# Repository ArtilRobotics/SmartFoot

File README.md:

# SmartInsole
hardware y Firmware del proyecto

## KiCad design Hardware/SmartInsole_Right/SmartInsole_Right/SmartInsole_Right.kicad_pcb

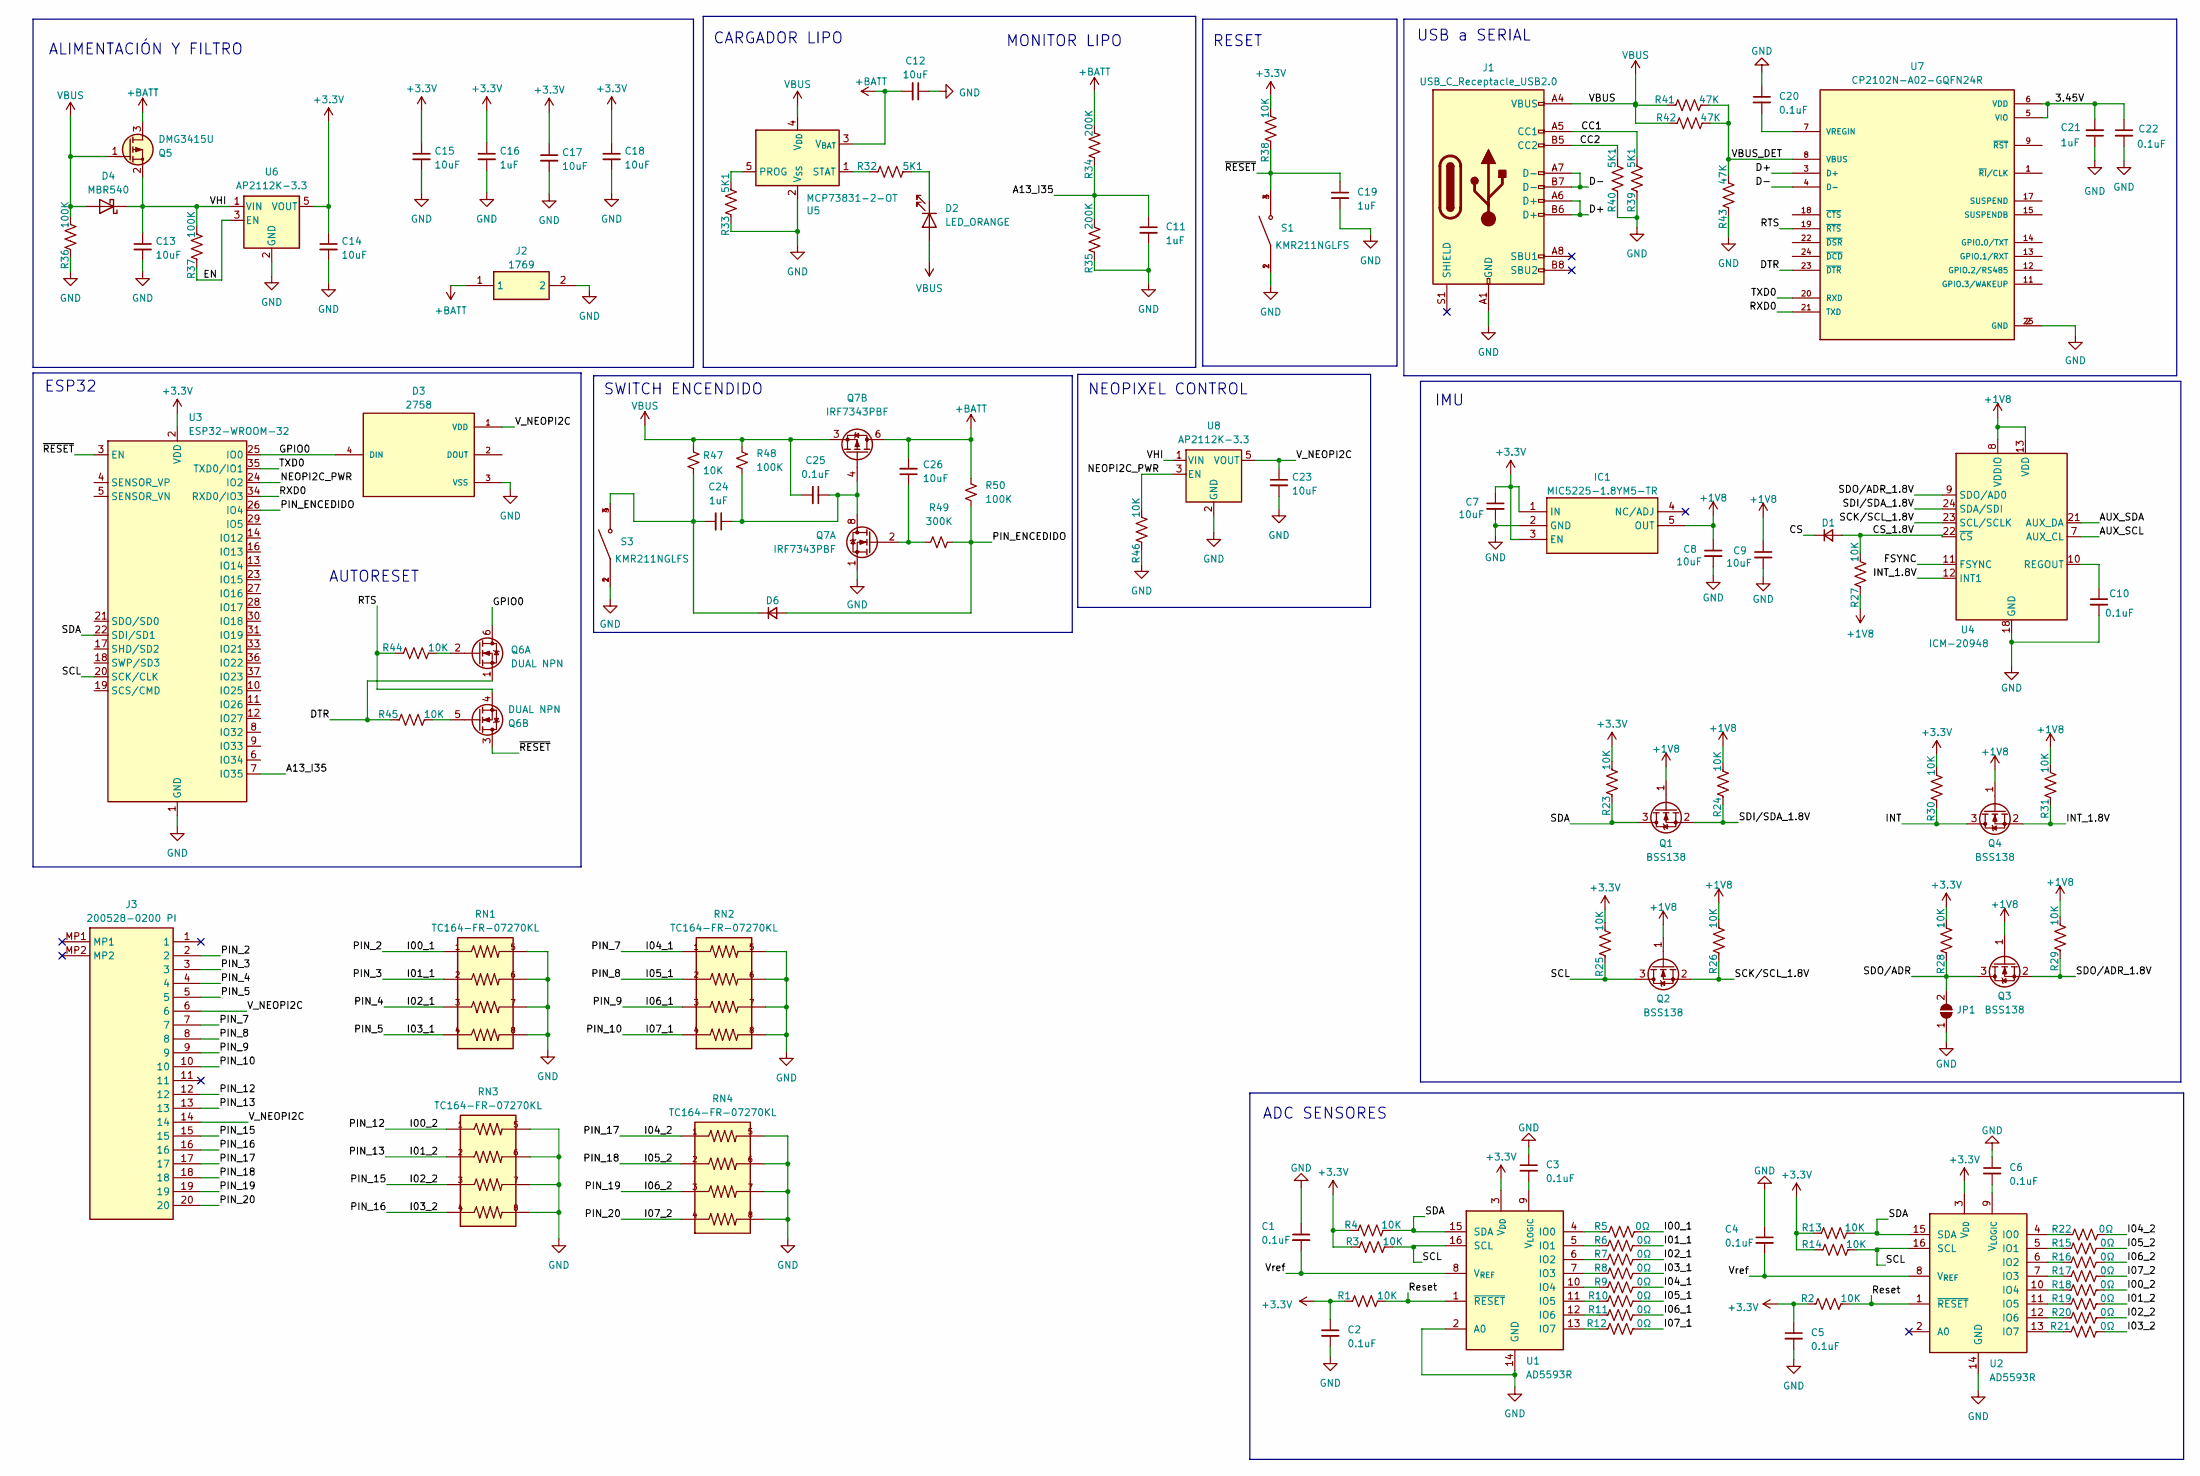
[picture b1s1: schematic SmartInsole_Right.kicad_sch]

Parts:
C1, C2, C3, C4, C5, C6, C10, C20, C22, C25: 0.1uF; C_0805
C7, C8, C9, C12, C13, C14, C15, C17, C18, C23, C26: 10uF; C_0805
C11, C16, C19, C21, C24: 1uF; C_0805
D1, D6: D_Small; D_0805_2012Metric
D2: LED_ORANGE; LED_0805_2012Metric
D3: 2758; SOL320P540X170-4N; PARTREV 01
D4: MBR540; D_SOD-123
IC1: MIC5225-1.8YM5-TR; SOT95P280X130-5N; Mouser Part Number 998-MIC5225-1.8YM5TR
J1: USB_C_Receptacle_USB2.0; USB_C_Receptacle_G-Switch_GT-USB-7010ASV
J2: 1769; Mouser Part Number 485-1769
J3: 200528-0200 PI; 2005280200; Mouser Part Number 538-200528-0200
JP1: SolderJumper_2_Open; SolderJumper-2_P1.3mm_Open_RoundedPad1.0x1.5mm
Q1, Q2, Q3, Q4: BSS138; SOT-23
Q5: DMG3415U; SOT-23
Q6: DUAL NPN
Q7: IRF7343PBF; SOIC-8_3.9x4.9mm_P1.27mm
R1, R2, R3, R4, R13, R14, R23, R24, R25, R26, R27, R28, R29, R30, R31, R38, R44, R45, R46, R47: 10K; R_0805_2012Metric
R5, R6, R7, R8, R9, R10, R11, R12, R15, R16, R17, R18, R19, R20, R21, R22: 0Ω; R_0805_2012Metric
R32, R33, R39, R40: 5K1; R_0805_2012Metric
R34, R35: 200K; R_0805_2012Metric
R36, R37, R48, R50: 100K; R_0805_2012Metric
R41, R42, R43: 47K; R_0805_2012Metric
R49: 300K; R_0805_2012Metric
RN1, RN2, RN3, RN4: TC164-FR-07270KL; RESCAV80P320X160X70-8N
S1, S3: KMR211NGLFS; SW_KMR211NGLFS; PARTREV 8 jun 16
U1, U2: AD5593R; TSSOP-16_4.4x5mm_P0.65mm
U3: ESP32-WROOM-32
U4: ICM-20948; InvenSense_QFN-24_3x3mm_P0.4mm
U5: MCP73831-2-OT; SOT-23-5
U6, U8: AP2112K-3.3; SOT-23-5
U7: CP2102N-A02-GQFN24R; QFN50P400X400X80-25N; PARTREV 1.3

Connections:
+1V8: C8.1, C9.1, IC1.5 (OUT), Q1.1 (G), Q2.1 (G), Q3.1 (G), Q4.1 (G), R24.2, R26.2, R27.1, R29.2, R31.2, U4.8 (VDDIO), U4.13 (VDD)
+3V3: C2.1, C5.1, C7.1, C14.1, C15.1, C16.1, C17.1, C18.1, IC1.1 (IN), IC1.3 (EN), R1.1, R2.1, R3.1, R4.1, R13.1, R14.1, R23.2, R25.2, R28.2, R30.2, R38.2, U1.3 (V_{DD}), U2.3 (V_{DD}), U3.2 (VDD), U6.5 (VOUT)
+BATT: C12.2, C26.2, J2.1, Q5.3 (D), Q7.5 (D), Q7.6 (D), R34.2, R50.1, U5.3 (V_{BAT})
/3.45V: C21.2, C22.1, U7.5 (VIO), U7.6 (VDD)
/A13_I35: C11.1, R34.1, R35.2, U3.7 (IO35)
/AUX_SCL: U4.7 (AUX_CL)
/AUX_SDA: U4.21 (AUX_DA)
/CC1: J1.A5 (CC1), R39.2
/CC2: J1.B5 (CC2), R40.2
/CS: D1.1 (K)
/CS_1.8V: D1.2 (A), R27.2, U4.22 (~CS)
/D+: J1.A6 (D+), J1.B6 (D+), U7.3 (D+)
/D-: J1.A7 (D-), J1.B7 (D-), U7.4 (D-)
/DTR: Q6.1 (S), R45.1, U7.23 (~DTR)
/EN: R37.1, U6.3 (EN)
/FSYNC: U4.11 (FSYNC)
/GPIO0: D3.4 (DIN), Q6.6 (D), U3.25 (IO0)
/I00_1: J3.2, R5.2, RN1.1
/I00_2: J3.12, R18.2, RN3.1
/I01_1: J3.3, R6.2, RN1.2
/I01_2: J3.13, R19.2, RN3.2
/I02_1: J3.4, R7.2, RN1.3
/I02_2: J3.15, R20.2, RN3.3
/I03_1: J3.5, R8.2, RN1.4
/I03_2: J3.16, R21.2, RN3.4
/I04_1: J3.7, R9.2, RN2.1
/I04_2: J3.17, R22.2, RN4.1
/I05_1: J3.8, R10.2, RN2.2
/I05_2: J3.18, R15.2, RN4.2
/I06_1: J3.9, R11.2, RN2.3
/I06_2: J3.19, R16.2, RN4.3
/I07_1: J3.10, R12.2, RN2.4
/I07_2: J3.20, R17.2, RN4.4
/INT: Q4.3 (D), R30.1
/INT_1.8V: Q4.2 (S), R31.1, U4.12 (INT1)
/NEOPI2C_PWR: R46.2, U3.24 (IO2), U8.3 (EN)
/PIN_ENCEDIDO: D6.2 (A), R49.1, R50.2, U3.26 (IO4)
/RTS: Q6.4 (S), R44.1, U7.19 (~RTS)
/RXD0: U3.34 (RXD0/IO3), U7.21 (TXD)
/Reset: R1.2, R2.2, U1.1 (~RESET), U2.1 (~RESET)
/SCK/SCL_1.8V: Q2.2 (S), R26.1, U4.23 (SCL/SCLK)
/SCL: Q2.3 (D), R3.2, R14.2, R25.1, U1.16 (SCL), U2.16 (SCL), U3.20 (SCK/CLK)
/SDA: Q1.3 (D), R4.2, R13.2, R23.1, U1.15 (SDA), U2.15 (SDA), U3.22 (SDI/SD1)
/SDI/SDA_1.8V: Q1.2 (S), R24.1, U4.24 (SDA/SDI)
/SDO/ADR: JP1.2 (B), Q3.3 (D), R28.1
/SDO/ADR_1.8V: Q3.2 (S), R29.1, U4.9 (SDO/AD0)
/TXD0: U3.35 (TXD0/IO1), U7.20 (RXD)
/VBUS_DET: R41.2, R42.2, R43.2, U7.8 (VBUS)
/VHI: C13.1, D4.1 (K), Q5.2 (S), R37.2, U6.1 (VIN), U8.1 (VIN)
/V_NEOPI2C: C23.1, D3.1 (VDD), J3.6, J3.14, U8.5 (VOUT)
/Vref: C1.2, C4.2, U1.8 (V_{REF}), U2.8 (V_{REF})
/~RESET: C19.1, Q6.3 (D), R38.1, S1.3, S1.4, U3.3 (EN)
GND: C1.1, C2.2, C3.1, C4.1, C5.2, C6.1, C7.2, C8.2, C9.2, C10.2, C11.2, C12.1, C13.2, C14.2, C15.2, C16.2, C17.2, C18.2, C19.2, C20.1, C21.1, C22.2, C23.2, D3.3 (VSS), IC1.2 (GND), J1.A1 (GND), J1.A12 (GND), J1.B1 (GND), J1.B12 (GND), J2.2, JP1.1 (A), Q7.1 (S), R33.1, R35.1, R36.1, R39.1, R40.1, R43.1, R46.1, RN1.5, RN1.6, RN1.7, RN1.8, RN2.5, RN2.6, RN2.7, RN2.8, RN3.5, RN3.6, RN3.7, RN3.8, RN4.5, RN4.6, RN4.7, RN4.8, S1.1, S1.2, S3.1, S3.2, U1.2 (A0), U1.14 (GND), U2.14 (GND), U3.1 (GND), U3.15 (GND), U3.38 (GND), U3.39 (GND), U4.18 (GND), U4.20 (GND), U5.2 (V_{SS}), U6.2 (GND), U7.2 (GND), U7.25 (GND), U8.2 (GND)
unnamed: D2.1 (K), R32.2
unnamed: C24.2, D6.1 (K), R47.2, S3.3, S3.4
unnamed: Q6.2 (G), R44.2
unnamed: Q6.5 (G), R45.2
unnamed: C26.1, Q7.2 (G), R49.2
unnamed: C24.1, C25.1, Q7.4 (G), Q7.7 (D), Q7.8 (D), R48.2
unnamed: R5.1, U1.4 (IO0)
unnamed: R6.1, U1.5 (IO1)
unnamed: R7.1, U1.6 (IO2)
unnamed: R8.1, U1.7 (IO3)
unnamed: R9.1, U1.10 (IO4)
unnamed: R10.1, U1.11 (IO5)
unnamed: R11.1, U1.12 (IO6)
unnamed: R12.1, U1.13 (IO7)
unnamed: C3.2, U1.9 (V_{LOGIC})
unnamed: R22.1, U2.4 (IO0)
unnamed: R15.1, U2.5 (IO1)
unnamed: R16.1, U2.6 (IO2)
unnamed: R17.1, U2.7 (IO3)
unnamed: R18.1, U2.10 (IO4)
unnamed: R19.1, U2.11 (IO5)
unnamed: R20.1, U2.12 (IO6)
unnamed: R21.1, U2.13 (IO7)
unnamed: C6.2, U2.9 (V_{LOGIC})
unnamed: C10.1, U4.10 (REGOUT)
unnamed: R33.2, U5.5 (PROG)
unnamed: R32.1, U5.1 (STAT)
unnamed: C20.2, U7.7 (VREGIN)
VBUS: C25.2, D2.2 (A), D4.2 (A), J1.A4 (VBUS), J1.A9 (VBUS), J1.B4 (VBUS), J1.B9 (VBUS), Q5.1 (G), Q7.3 (1), R36.2, R41.1, R42.1, R47.1, R48.1, U5.4 (V_{DD})

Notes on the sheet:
ALIMENTACIÓN Y FILTRO
NEOPIXEL CONTROL
MONITOR LIPO
ADC SENSORES
SWITCH ENCENDIDO
USB a SERIAL
RESET
AUTORESET
CARGADOR LIPO
ESP32
IMU

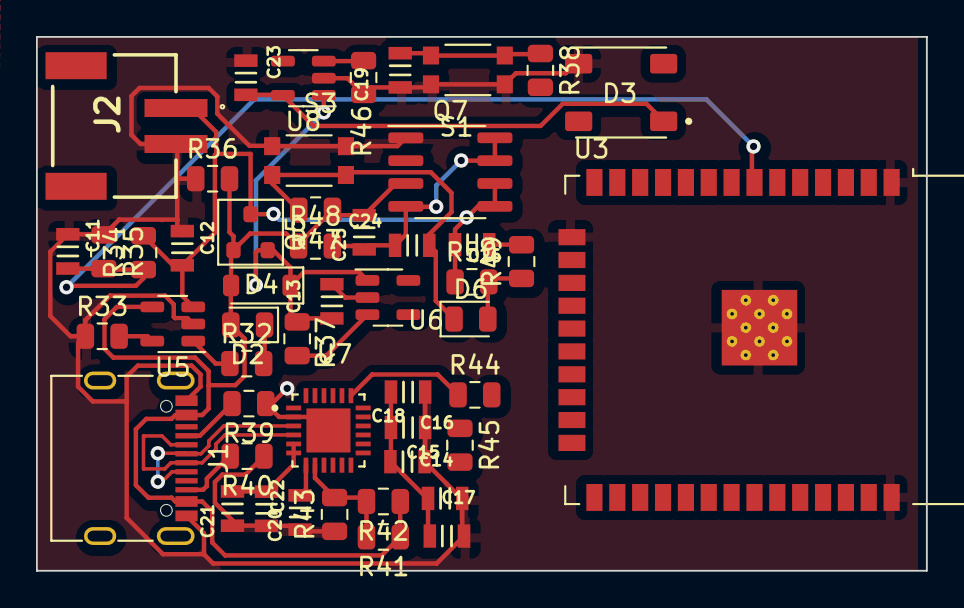
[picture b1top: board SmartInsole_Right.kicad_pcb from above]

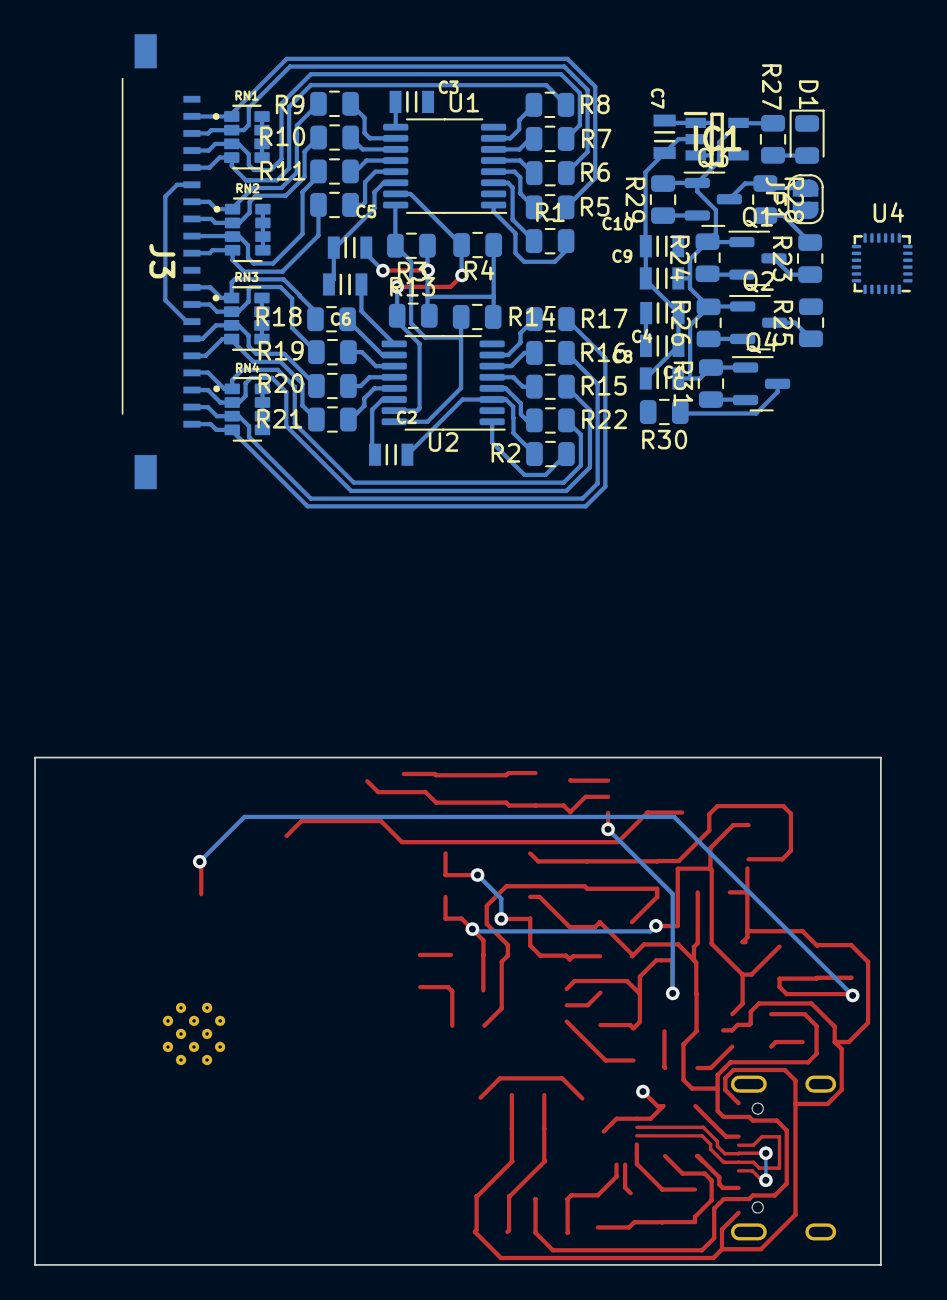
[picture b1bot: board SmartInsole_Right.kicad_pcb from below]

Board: 2 copper layers, 49.4 x 29.7 mm, 106 parts (56 on the bottom side), 76 nets.

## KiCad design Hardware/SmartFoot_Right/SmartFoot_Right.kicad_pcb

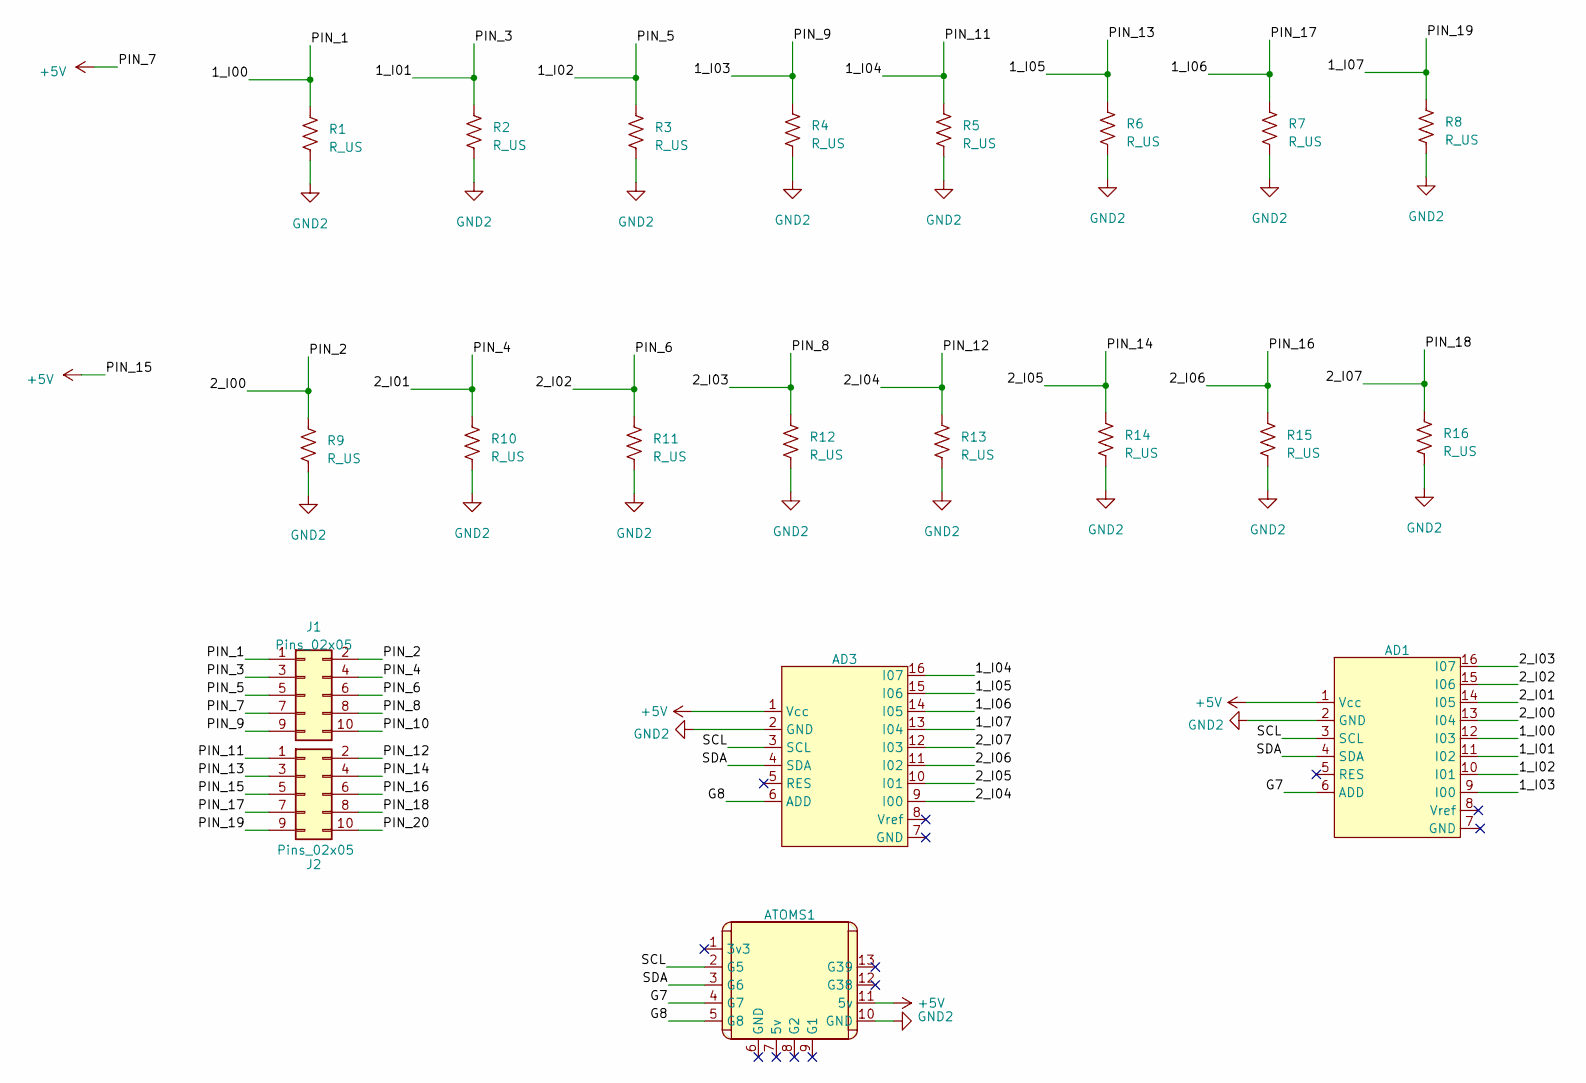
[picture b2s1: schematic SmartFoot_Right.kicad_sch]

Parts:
AD1, AD3: EC Buying AD5593
ATOMS1: ATOM_S3
J1, J2: Pins_02x05; Pins_2x05_2.54mm_TH; Part Number FTSH-105-01-F-DV
R1, R2, R3, R4, R5, R6, R7, R8, R9, R10, R11, R12, R13, R14, R15, R16: R_US; R_0805_2012Metric

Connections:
+5V: AD1.1 (Vcc), AD3.1 (Vcc), ATOMS1.11 (5v), J1.7, J2.5
/1_I00: AD1.12 (I03), J1.1, R1.1
/1_I01: AD1.11 (I02), J1.3, R2.1
/1_I02: AD1.10 (I01), J1.5, R3.1
/1_I03: AD1.9 (I00), J1.9, R4.1
/1_I04: AD3.16 (I07), J2.1, R5.1
/1_I05: AD3.15 (I06), J2.3, R6.1
/1_I06: AD3.14 (I05), J2.7, R7.1
/1_I07: AD3.13 (I04), J2.9, R8.1
/2_I00: AD1.13 (I04), J1.2, R9.1
/2_I01: AD1.14 (I05), J1.4, R10.1
/2_I02: AD1.15 (I06), J1.6, R11.1
/2_I03: AD1.16 (I07), J1.8, R12.1
/2_I04: AD3.9 (I00), J2.2, R13.1
/2_I05: AD3.10 (I01), J2.4, R14.1
/2_I06: AD3.11 (I02), J2.6, R15.1
/2_I07: AD3.12 (I03), J2.8, R16.1
/G7: AD1.6 (ADD), ATOMS1.4 (G7)
/G8: AD3.6 (ADD), ATOMS1.5 (G8)
/PIN_10: J1.10
/PIN_20: J2.10
/SCL: AD1.3 (SCL), AD3.3 (SCL), ATOMS1.2 (G5)
/SDA: AD1.4 (SDA), AD3.4 (SDA), ATOMS1.3 (G6)
GND2: AD1.2 (GND), AD3.2 (GND), ATOMS1.10 (GND), R1.2, R2.2, R3.2, R4.2, R5.2, R6.2, R7.2, R8.2, R9.2, R10.2, R11.2, R12.2, R13.2, R14.2, R15.2, R16.2

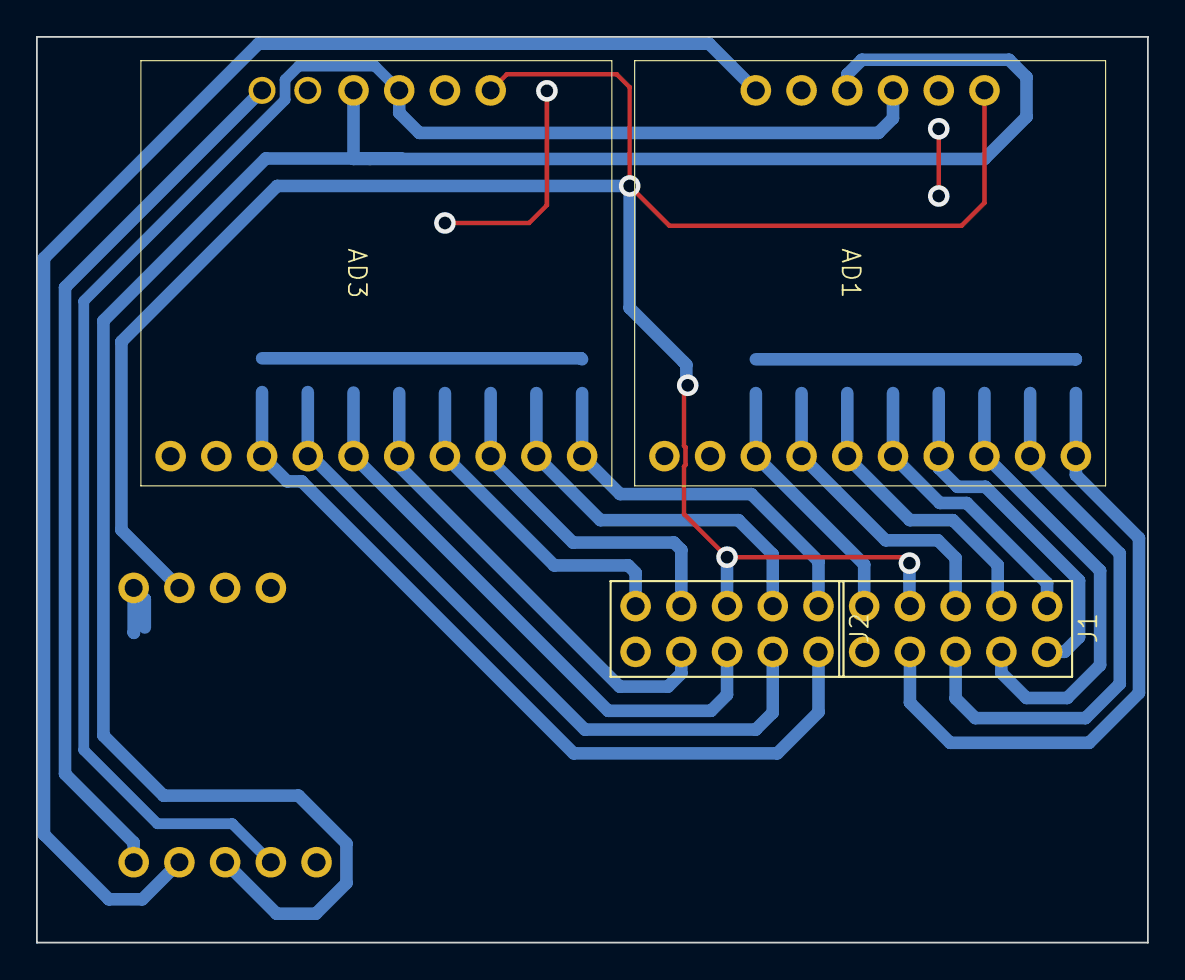
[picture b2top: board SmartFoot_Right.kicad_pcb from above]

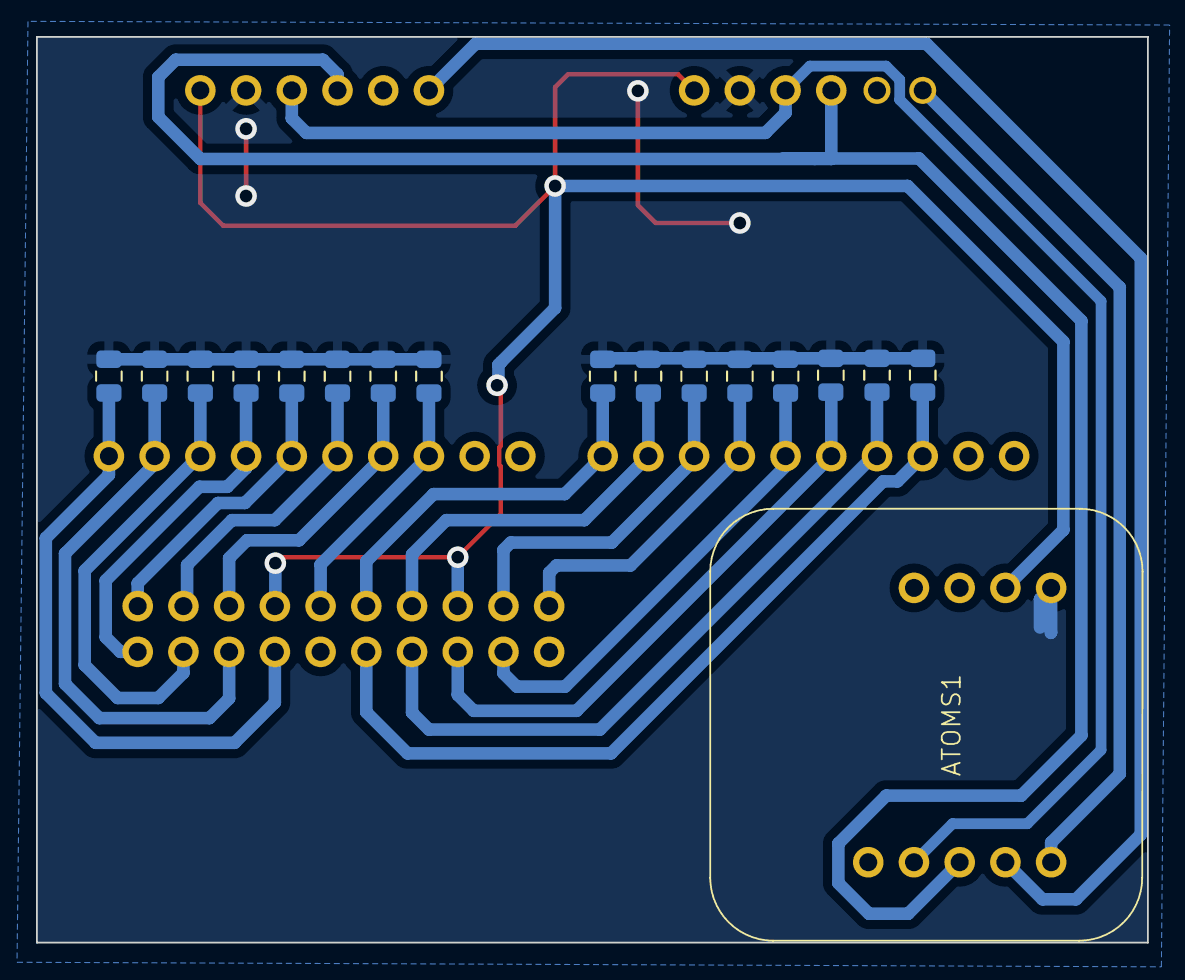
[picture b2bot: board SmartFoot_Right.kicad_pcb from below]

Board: 2 copper layers, 61.7 x 50.3 mm, 21 parts (17 on the bottom side), 22 nets.

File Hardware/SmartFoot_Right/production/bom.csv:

Designator,Footprint,Quantity,Value,LCSC Part #
"AD1, AD3",EC Buying AD5593,2,~,
ATOMS1,ATOM_S3,1,~,
"J1, J2",Pins_2x05_2.54mm_TH,2,Pins_02x05,
"R1, R10, R11, R12, R13, R14, R15, R16, R2, R3, R4, R5, R6, R7, R8, R9",0805,16,R_US,

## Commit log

2023-11-27 feat: added SmartInsole SMD PCB
2023-11-27 feat: Added component libraries
2023-11-27 feat: change component position
2023-11-27 feat: added project libraries
2023-11-27 feat: added 3D
2023-11-27 feat: added more libraries
2023-11-27 feat: change 3D
